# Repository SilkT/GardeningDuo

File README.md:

# GardeningDuo
ESP8266 based automated plants watering
Project is based on ESP8266 Wi-Fi enabled microcontroller and use of two analog moisture sensors. The data is logged from said sensors and compared to values stored in cloud represented by google spreadsheet accesed by connecting to internet. In case of necessity, the relay on board is triggered and the plant is watered using the connected pump. Information from sensors is also logged and stored in a spreadsheet, where is can be displayed as a graph. Hardware part of the project consists of esp12e breakout board, dual moisture sensors, and two relays that control the pumps. For software, Arduino IDE is used because of high availability of  open source code and simplicity of work with esp8266 chips.
Only Hardware part is avalible in this repo at the moment.

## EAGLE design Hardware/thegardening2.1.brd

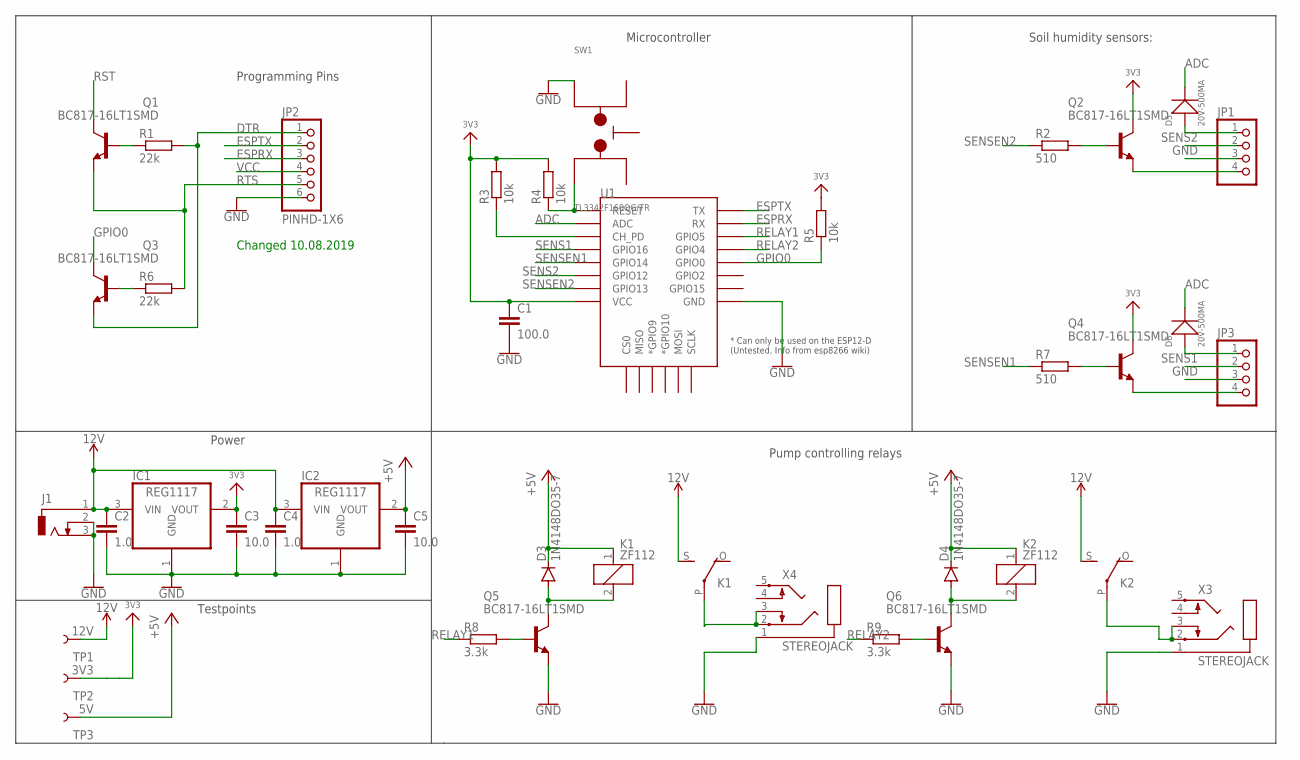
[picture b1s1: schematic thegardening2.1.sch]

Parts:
C1: 100.0; C0805
C2, C4: 1.0; C0805
C3, C5: 10.0; C0805
D3, D4: 1N4148DO35-7; DO35-7
D5, D6: 20V-500MA; SOD-123
IC1, IC2: REG1117; SOT223
J1: DCJ0303
JP1, JP3: PINHD-1X4; 1X04
JP2: PINHD-1X6; 1X06
K1, K2: ZF112
Q1, Q2, Q3, Q4, Q5, Q6: BC817-16LT1SMD; SOT23-BEC
R1, R6: 22k; R0805
R2, R7: 510; R0805
R3, R4, R5: 10k; R0805
R8, R9: 3.3k; R0805
SW1: TL3342F160QG/TR
TP1: 12V; TP_15TH
TP2: 3V3; TP_15TH
TP3: 5V; TP_15TH
U1: ESP12ESMD; ESP12E-SMD
X3, X4: STEREOJACK; STX3100

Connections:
+5V: C5.1, D3.C, D4.C, IC2.2 (VOUT), K1.1, K2.1, TP3.P$1
ADC: D5.-, D6.-, U1.ADC
DTR: JP2.1, Q3.E, R1.2
ESPRX: JP2.3, U1.RXD0 (RX)
ESPTX: JP2.2, U1.TXD0 (TX)
GND: C1.2, C2.2, C3.2, C4.2, C5.2, IC1.1 (GND), IC2.1 (GND), J1.2, J1.3, JP1.3, JP2.6, JP3.3, Q5.E, Q6.E, SW1.3, U1.GND, X3.1, X4.1
GPIO0: Q3.C, R5.1, U1.GPIO0
unnamed: D3.A, K1.2, Q5.C
unnamed: K1.P, X4.2, X4.3
unnamed: D5.+, JP1.1
unnamed: D4.A, K2.2, Q6.C
unnamed: K2.P, X3.2, X3.3
unnamed: JP3.4, Q4.E
unnamed: JP1.4, Q2.E
unnamed: Q2.B, R2.2
unnamed: Q4.B, R7.2
unnamed: D6.+, JP3.1
unnamed: Q1.B, R1.1
unnamed: Q3.B, R6.1
unnamed: R3.1, U1.CH_PD
unnamed: Q5.B, R8.2
RELAY1: R8.1, U1.GPIO5
RELAY02: Q6.B, R9.2
RELAY2: R9.1, U1.GPIO4
RST: Q1.C, R4.1, SW1.1, U1.RESET
RTS: JP2.5, Q1.E, R6.2
SENS1: JP3.2, U1.GPIO16
SENS2: JP1.2, U1.GPIO12
SENSEN1: R7.1, U1.GPIO14
SENSEN2: R2.1, U1.GPIO13
VCC: C1.1, C3.1, IC1.2 (VOUT), JP2.4, Q2.C, Q4.C, R3.2, R4.2, R5.2, TP2.P$1, U1.VCC
VCC_2: C2.1, C4.1, IC1.3 (VIN), IC2.3 (VIN), J1.1, K1.S, K2.S, TP1.P$1

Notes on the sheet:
Programming Pins
Microcontroller
Soil humidity sensors:
Pump controlling relays
Power
Testpoints
Changed 10.08.2019

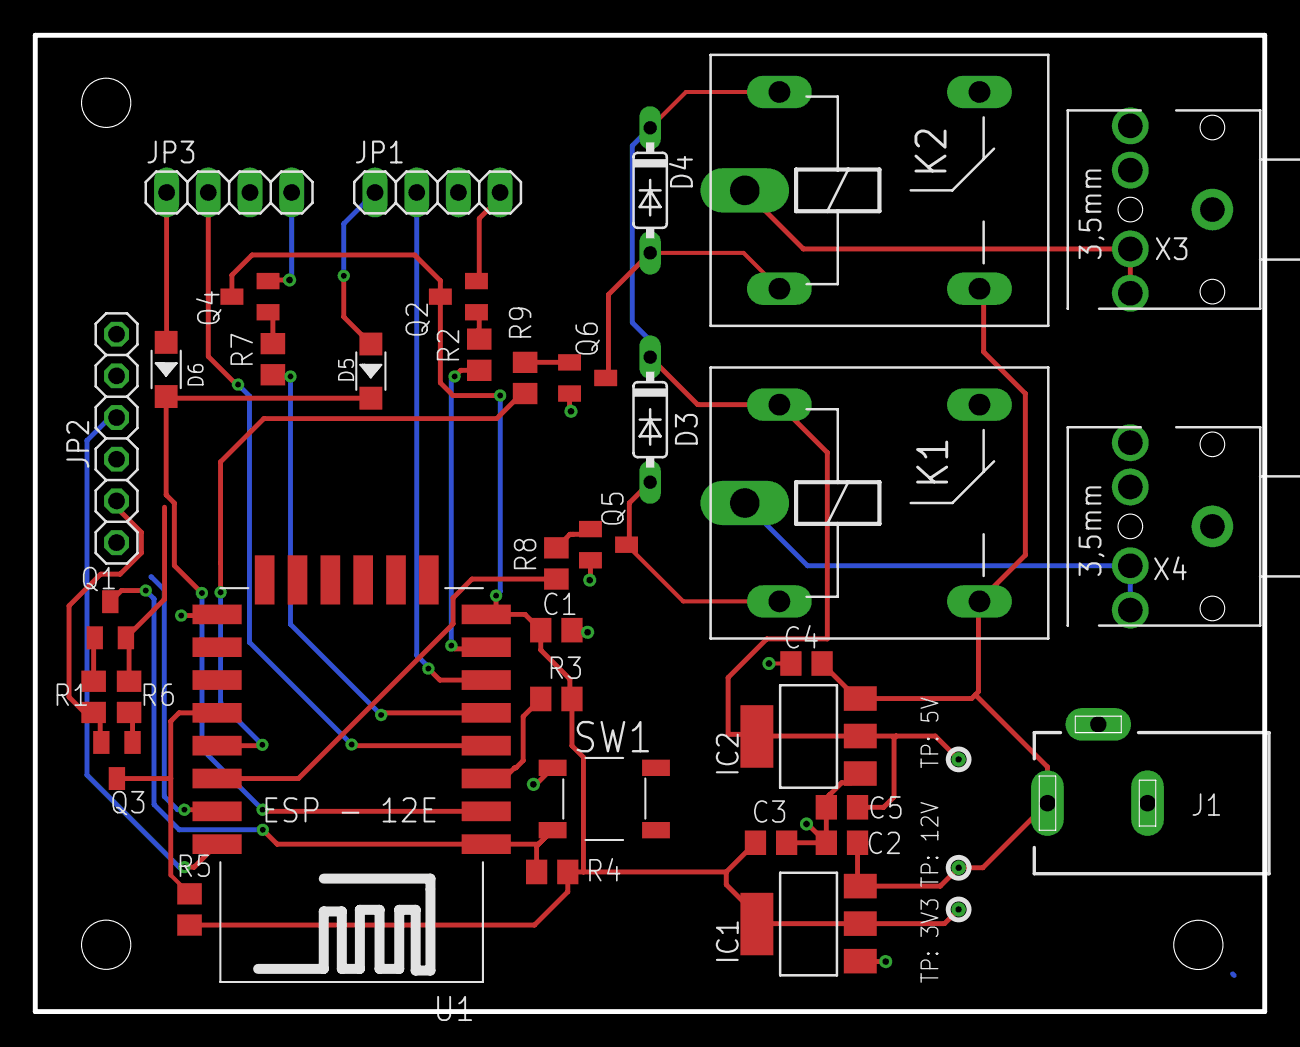
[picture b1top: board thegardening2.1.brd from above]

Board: 2 copper layers, 74.9 x 59.5 mm, 39 parts (0 on the bottom side), 32 nets.

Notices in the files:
parts and their libraries:
SparkFun-Connectors: Licensing: Creative Commons ShareAlike 4.0 International - https://creativecommons.org/licenses/by-sa/4.0
